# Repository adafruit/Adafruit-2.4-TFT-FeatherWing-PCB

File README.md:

## Adafruit 2.4 TFT FeatherWing PCB

<a href="http://www.adafruit.com/products/3315"><br/>
Click here to purchase one from the Adafruit shop</a>

PCB files for the Adafruit 2.4" TFT FeatherWing. Format is EagleCAD schematic and board layout
* https://www.adafruit.com/products/3315

### Description

A Feather board without ambition is a Feather board without FeatherWings! Spice up your Feather project with a beautiful 2.4" touchscreen display shield with built in microSD card socket. This TFT display is 2.4" diagonal with a bright 4 white-LED backlight. You get  240x320 pixels with individual 16-bit color pixel control. It has way more resolution than a black and white 128x64 display. As a bonus, this display comes with a resistive touchscreen attached to it already, so you can detect finger presses anywhere on the screen.

This FeatherWing uses a SPI display so it works fast on each and every one of our Feathers. We also include an SPI resistive touchscreen controller so you only need one additional pin to add a high quality touchscreen controller. One more pin is used for an optional SD card that can be used for storing images for display.

This Wing comes fully assembled with dual sockets for your Feather to plug into. You get two sockets per pin so you can plug in wires if you want to connect to Feather pins. Alternatively, each pin has a large square pad on the PCB for direct soldering.

Four mounting holes make it easy to attach this Wing anywhere. We also include a big reset button and an on/off switch connected to the Feather Enable pin (note that the Teensy 3.x Feather does not use the Enable pin so the switch will not do anything with that type).

New! As of Oct 11, 2023 we've made a big redesign to this product: We now use the TSC2007 instead of the discontinued STMPE811 touchscreen controller. The screen and micro SD card are the same but any touchscreen code will need to be updated to use our Arduino or CircuitPython library. We've also updated the reset button to be right-angle and added a STEMMA QT port.

### License

Adafruit invests time and resources providing this open source design, please support Adafruit and open-source hardware by purchasing products from [Adafruit](https://www.adafruit.com)!

Designed by Limor Fried/Ladyada for Adafruit Industries.

Creative Commons Attribution/Share-Alike, all text above must be included in any redistribution. See license.txt for additional details.

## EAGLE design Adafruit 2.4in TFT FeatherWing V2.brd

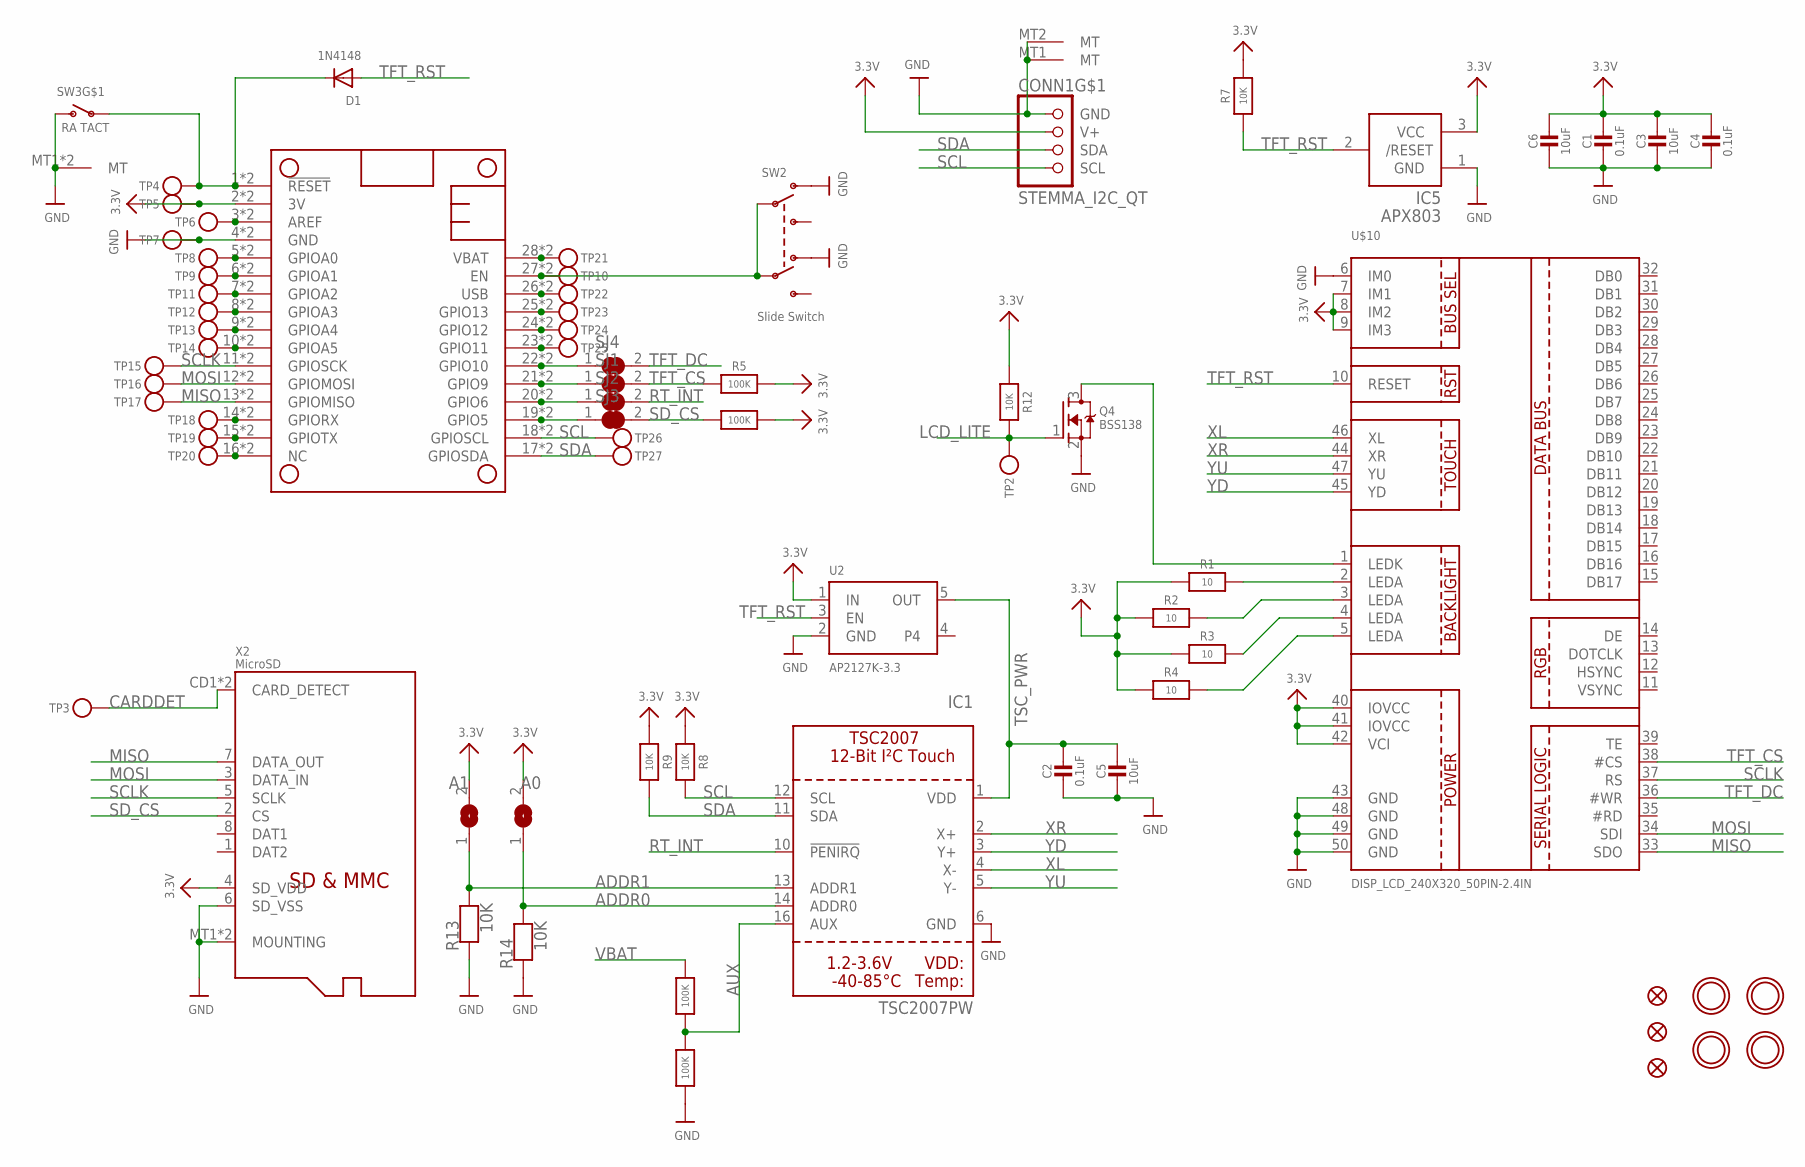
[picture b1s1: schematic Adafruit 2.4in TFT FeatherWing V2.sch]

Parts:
C1, C2, C4: 0.1uF; 0603-NO
C3, C5, C6: 10uF; 0805-NO
CONN1: STEMMA_I2C_QT; JST_SH4
D1: 1N4148; SOD-323
FID1, FID2, FID3: FIDUCIAL_1MM
IC1: TSC2007PW; TSSOP16
IC5: APX803; SOT23
ICSP_CLK1: A1; SOLDERJUMPER_ARROW_NOPASTE
ICSP_CLK2: A0; SOLDERJUMPER_ARROW_NOPASTE
MS2: FEATHERWING_SMTDUAL; FEATHERWING_SMT2
Q4: BSS138; SOT23-WIDE
R1, R2, R3, R4: 10; 0603-NO
R5, R6, R10, R11: 100K; 0603-NO
R7, R8, R9, R12, R13, R14: 10K; 0603-NO
SJ1, SJ2, SJ3, SJ4: SOLDERJUMPER_CLOSED; SOLDERJUMPER_CLOSEDWIRE
SW2: Slide Switch; EG1390
SW3: RA TACT; SPST_TACTILE_RA
TP2, TP3, TP4, TP5, TP6, TP7, TP8, TP9, TP10, TP11, TP12, TP13, TP14, TP15, TP16, TP17, TP18, TP19, TP20, TP21, TP22, TP23, TP24, TP25, TP26, TP27: TESTPOINTPAD2MM; TESTPOINT_PAD_2MM
U2: AP2127K-3.3; SOT23-5
U$9, U$11, U$15, U$17: MOUNTINGHOLE2.5; MOUNTINGHOLE_2.5_PLATED
U$10: DISP_LCD_240X320_50PIN-2.4IN; TFT_2.4IN_240X320_50PIN
X2: MicroSD; MICROSD

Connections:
3.3V: C1.1, C3.1, C4.1, C6.1, CONN1.2 (V+), IC5.3 (VCC), ICSP_CLK1.2, ICSP_CLK2.2, MS2.2 (3V), MS2.2' (3V), R1.1, R2.1, R3.1, R4.1, R5.2, R6.2, R7.2, R8.1, R9.1, R12.1, TP5.P$1, U2.1 (IN), U$10.7 (IM1), U$10.8 (IM2), U$10.9 (IM3), U$10.40 (IOVCC), U$10.41 (IOVCC), U$10.42 (VCI), X2.4 (SD_VDD)
!RESET: D1.C, MS2.1 (!RESET), MS2.1' (!RESET), SW3.1, TP4.P$1
A: MS2.5 (GPIOA0), MS2.5' (GPIOA0), TP8.P$1
ADDR0: IC1.14 (ADDR0), ICSP_CLK2.1, R14.2
ADDR1: IC1.13 (ADDR1), ICSP_CLK1.1, R13.2
AREF: MS2.3 (AREF), MS2.3' (AREF), TP6.P$1
AUX: IC1.16 (AUX), R10.1, R11.2
B: MS2.6 (GPIOA1), MS2.6' (GPIOA1), TP9.P$1
C: MS2.7 (GPIOA2), MS2.7' (GPIOA2), TP11.P$1
CARDDET: TP3.P$1, X2.CD1 (CARD_DETECT), X2.CD2 (CARD_DETECT)
D: MS2.8 (GPIOA3), MS2.8' (GPIOA3), TP12.P$1
E: MS2.9 (GPIOA4), MS2.9' (GPIOA4), TP13.P$1
EN: MS2.27 (EN), MS2.27' (EN), SW2.P1, SW2.P2, TP10.P$1
F: MS2.10 (GPIOA5), MS2.10' (GPIOA5), TP14.P$1
G: MS2.16 (NC), MS2.16' (NC), TP20.P$1
GND: C1.2, C2.2, C3.2, C4.2, C5.2, C6.2, CONN1.1 (GND), CONN1.MT1 (MT), CONN1.MT2 (MT), IC1.6 (GND), IC5.1 (GND), MS2.4 (GND), MS2.4' (GND), Q4.2 (S), R11.1, R13.1, R14.1, SW2.O1, SW2.O2, SW3.2 (S), SW3.MT1 (MT), SW3.MT2 (MT), TP7.P$1, U2.2 (GND), U$10.6 (IM0), U$10.43 (GND), U$10.48 (GND), U$10.49 (GND), U$10.50 (GND), X2.6 (SD_VSS), X2.MT1 (MOUNTING), X2.MT2 (MOUNTING)
H: MS2.19 (GPIO5), MS2.19' (GPIO5), SJ3.1
I: MS2.20 (GPIO6), MS2.20' (GPIO6), SJ2.1
J: MS2.21 (GPIO9), MS2.21' (GPIO9), SJ1.1
K: MS2.22 (GPIO10), MS2.22' (GPIO10), SJ4.1
L: MS2.23 (GPIO11), MS2.23' (GPIO11), TP25.P$1
LCD_LITE: Q4.1 (G), R12.2, TP2.P$1
M: MS2.24 (GPIO12), MS2.24' (GPIO12), TP24.P$1
MISO: MS2.13 (GPIOMISO), MS2.13' (GPIOMISO), TP17.P$1, U$10.33 (SDO), X2.7 (DATA_OUT)
MOSI: MS2.12 (GPIOMOSI), MS2.12' (GPIOMOSI), TP16.P$1, U$10.34 (SDI), X2.3 (DATA_IN)
N: MS2.25 (GPIO13), MS2.25' (GPIO13), TP23.P$1
unnamed: R4.2, U$10.5 (LEDA)
unnamed: R1.2, U$10.2 (LEDA)
unnamed: R2.2, U$10.3 (LEDA)
unnamed: R3.2, U$10.4 (LEDA)
unnamed: Q4.3 (D), U$10.1 (LEDK)
RT_INT: IC1.10 (!PENIRQ), SJ2.2
RX: MS2.14 (GPIORX), MS2.14' (GPIORX), TP18.P$1
SCL: CONN1.4 (SCL), IC1.12 (SCL), MS2.18 (GPIOSCL), MS2.18' (GPIOSCL), R8.2, TP26.P$1
SCLK: MS2.11 (GPIOSCK), MS2.11' (GPIOSCK), TP15.P$1, U$10.37 (RS), X2.5 (SCLK)
SDA: CONN1.3 (SDA), IC1.11 (SDA), MS2.17 (GPIOSDA), MS2.17' (GPIOSDA), R9.2, TP27.P$1
SD_CS: R6.1, SJ3.2, X2.2 (CS)
TFT_CS: R5.1, SJ1.2, U$10.38 (#CS)
TFT_DC: SJ4.2, U$10.36 (#WR)
TFT_RST: D1.A, IC5.2 (/RESET), R7.1, U2.3 (EN), U$10.10 (RESET)
TSC_PWR: C2.1, C5.1, IC1.1 (VDD), U2.5 (OUT)
TX: MS2.15 (GPIOTX), MS2.15' (GPIOTX), TP19.P$1
USB: MS2.26 (USB), MS2.26' (USB), TP22.P$1
VBAT: MS2.28 (VBAT), MS2.28' (VBAT), R10.2, TP21.P$1
XL: IC1.4 (X-), U$10.46 (XL)
XR: IC1.2 (X+), U$10.44 (XR)
YD: IC1.3 (Y+), U$10.45 (YD)
YU: IC1.5 (Y-), U$10.47 (YU)

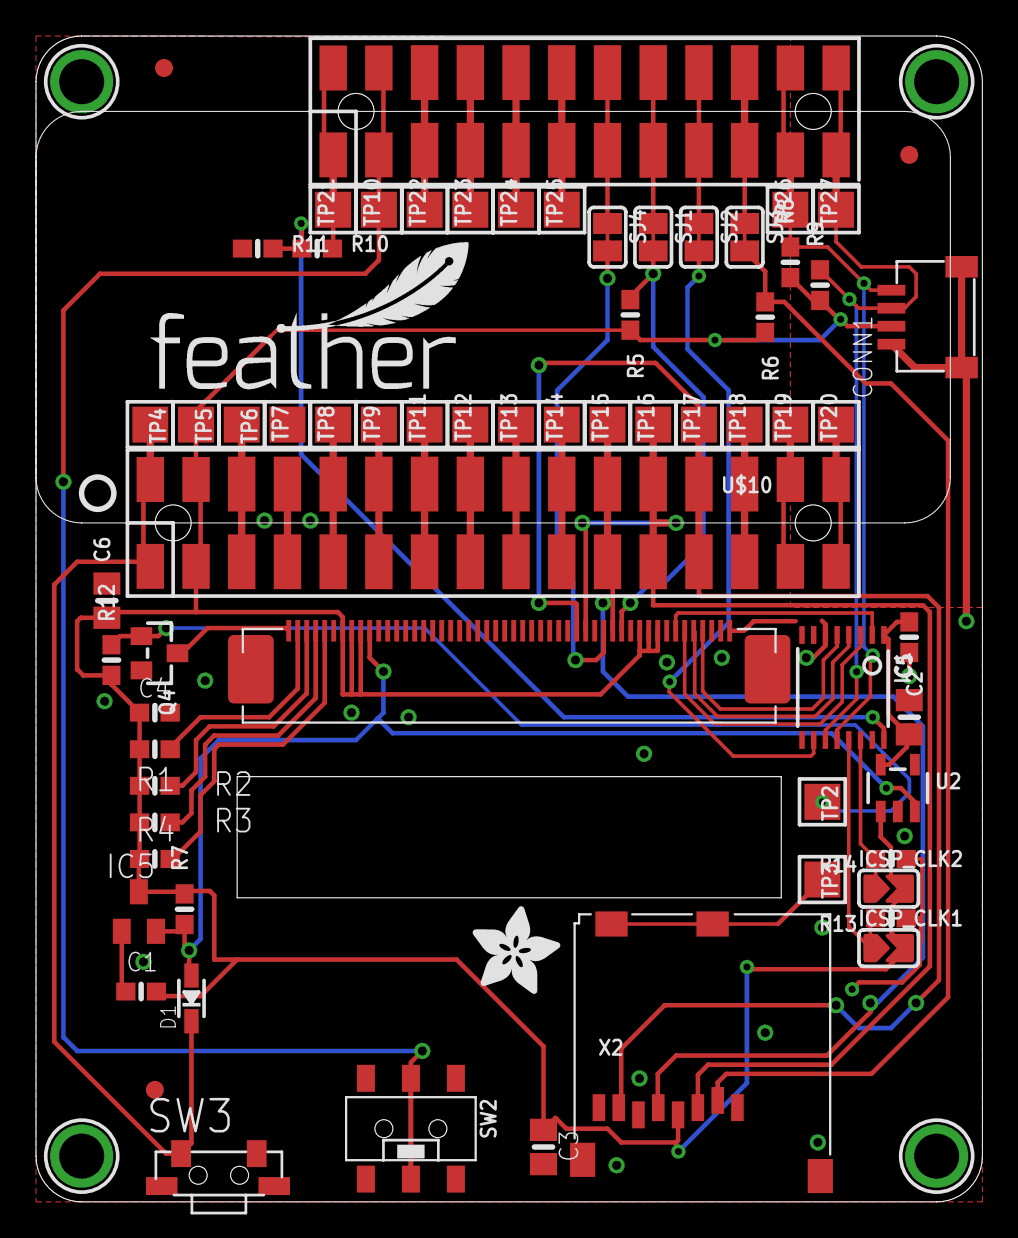
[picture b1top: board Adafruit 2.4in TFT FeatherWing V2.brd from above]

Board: 2 copper layers, 52.6 x 64.8 mm, 87 parts (1 on the bottom side), 48 nets.

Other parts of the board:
PLABEL0: PLABEL0
PLABEL1: PLABEL1
PLABEL2: PLABEL2
PLABEL3: PLABEL3
PLABEL4: PLABEL4
PLABEL5: PLABEL5
PLABEL6: PLABEL6
PLABEL7: PLABEL7
PLABEL8: PLABEL8
PLABEL9: PLABEL9
PLABEL10: PLABEL10
PLABEL11: PLABEL11
PLABEL12: PLABEL12
PLABEL13: PLABEL13
U$29: FEATHERLOGO_MED
U$30: ADAFRUIT_5MM
U$34: PCBFEAT-REV-040

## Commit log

2016-11-09 inity
2023-10-20 adding V2 files
